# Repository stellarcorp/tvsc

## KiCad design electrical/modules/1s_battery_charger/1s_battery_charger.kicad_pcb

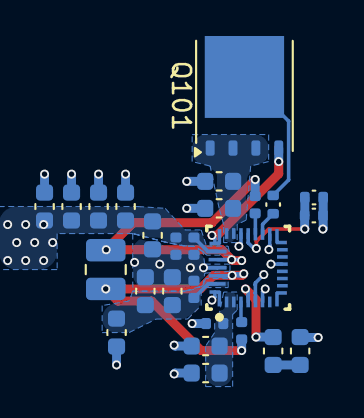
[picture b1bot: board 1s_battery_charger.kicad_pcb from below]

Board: 4 copper layers, 26 parts (26 on the bottom side), 15 nets.

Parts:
C101, C102, C104, C105, C107, C108, C111, C112, C114, C116, C117, C118, C119, C120: 10u; Nondescript_C_0603_1608Metric
C103, C106, C113, C115: 100n; Nondescript_C_0402_1005Metric
C109, C110: 0.047u; Nondescript_C_0402_1005Metric
L101: 2.2µH; L_1008_2520Metric
Q101: CSD16570Q5B; TDSON-8-1
R101, R102: 9k31; Nondescript_R_0402_1005Metric
R103: 100; Nondescript_R_0402_1005Metric
U101: BQ25798; RQM0029A-MFG

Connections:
/BATT_VIN: C101.1, C102.1, C103.1, U101.2 (VBUS), U101.3 (VBUS)
/REGN: C104.1, U101.5 (REGN), U101.17 (ILIM_HIZ)
/SYS: C113.1, C115.1, C116.1, C117.1, C118.1, C119.1, C120.1, U101.25 (SYS)
/VBATT: Q101.5 (D), R103.2
GND: C101.2, C102.2, C103.2, C105.2, C106.2, C107.2, C108.2, C111.2, C112.2, C113.2, C114.2, C115.2, C116.2, C117.2, C118.2, C119.2, C120.2, R101.2, R102.2, U101.13 (~CE), U101.27 (GND)
unnamed: C104.2, C105.1
unnamed: C111.1, C114.1, Q101.1 (S), Q101.2 (S), Q101.3 (S), U101.22 (BAT), U101.23 (BAT)
unnamed: Q101.4 (G), U101.24 (SDRV)
unnamed: R103.1, U101.18 (BATP)
unnamed: C109.1, U101.4 (BTST1)
unnamed: C110.1, U101.19 (BTST2)
unnamed: C106.1, C107.1, C108.1, C112.1, U101.29 (PMID)
unnamed: R101.1, R102.1, U101.20 (PROG)
unnamed: C109.2, L101.2, U101.28 (SW1)
unnamed: C110.2, L101.1, U101.26 (SW2)

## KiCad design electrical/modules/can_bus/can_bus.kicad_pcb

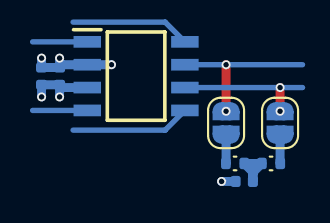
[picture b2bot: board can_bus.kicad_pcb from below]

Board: 4 copper layers, 8 parts (8 on the bottom side), 7 nets.

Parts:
C701: 1u; Nondescript_C_0402_1005Metric
C702, C703: 100n; Nondescript_C_0402_1005Metric
JP701, JP702: SolderJumper_2_Open; SolderJumper-2_P1.3mm_Open_RoundedPad1.0x1.5mm
R701, R702: 60; Nondescript_R_0402_1005Metric
U701: TCAN330DR; SOIC127P600X175-8N

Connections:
/3V3: C701.1, C702.1, U701.3 (VCC)
/CANH: JP701.1 (A), U701.7 (CANH)
/CANH_TERMINATION: JP701.2 (B), R701.1
/CANL: JP702.2 (B), U701.6 (CANL)
/CANL_TERMINATION: JP702.1 (A), R702.2
GND: C701.2, C702.2, C703.1, U701.2 (GND)
unnamed: C703.2, R701.2, R702.1

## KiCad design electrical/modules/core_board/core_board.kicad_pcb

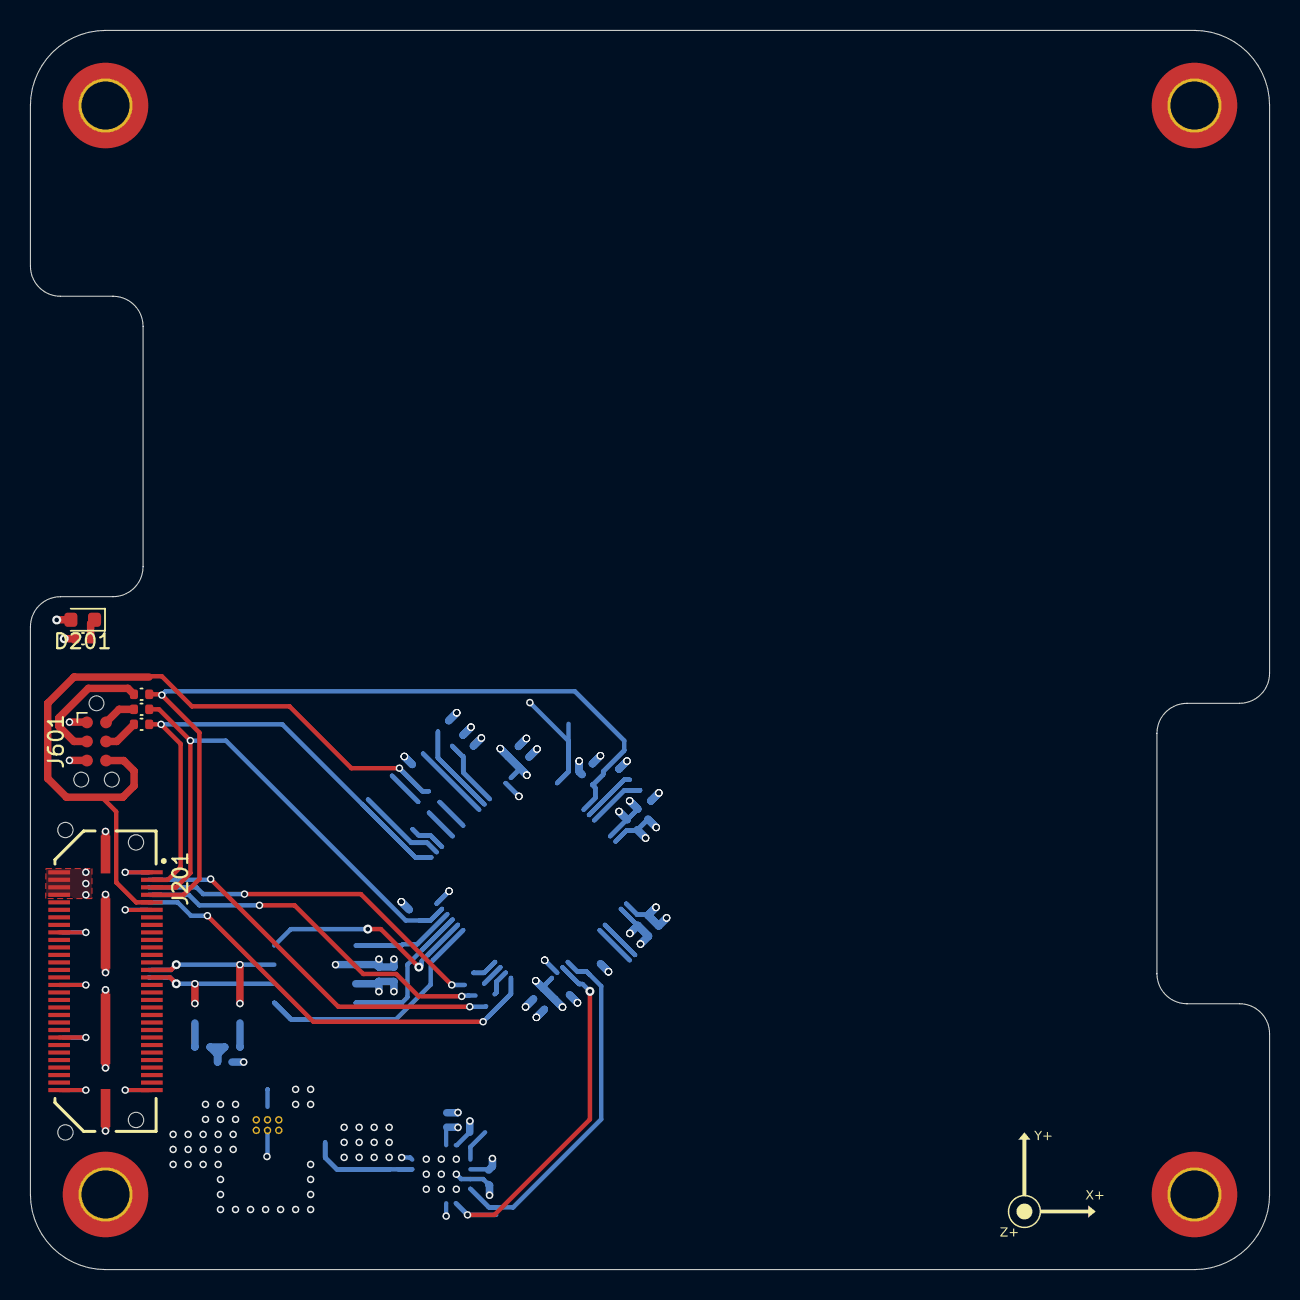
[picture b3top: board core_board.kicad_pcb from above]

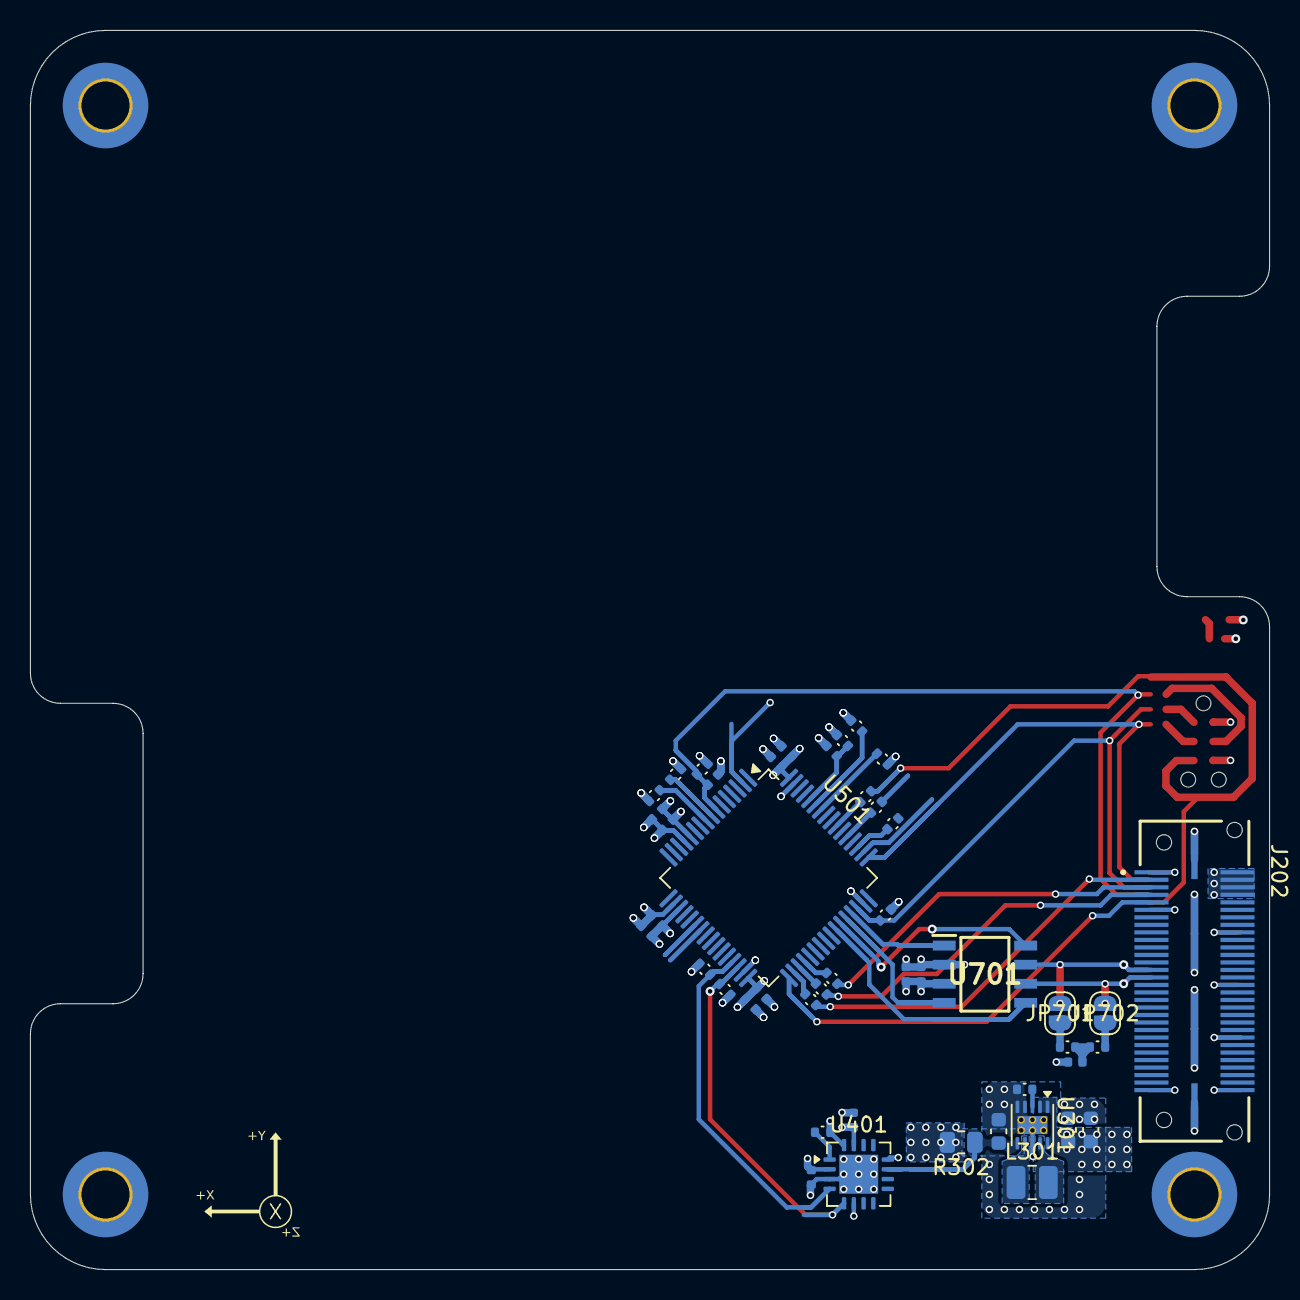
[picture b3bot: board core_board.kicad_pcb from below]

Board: 4 copper layers, 82.5 x 82.5 mm, 54 parts (46 on the bottom side), 44 nets.

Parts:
C301, C303: 22u; Nondescript_C_0603_1608Metric
C302: 10u; Nondescript_C_0603_1608Metric
C401, C402, C501, C502, C504, C506, C507, C509, C702, C703: 100n; Nondescript_C_0402_1005Metric
C503, C505, C508, C510, C701: 1u; Nondescript_C_0402_1005Metric
D201: Debug; LED_0603_1608Metric
J201: QTH-030-07-L-D-A; SAMTEC_QTH-030-07-L-D-A
J202: QSH-030-01-L-D-A; SAMTEC_QSH-030-01-L-D-A
J601: STLINK; Tag-Connect_TC2030-IDC-NL_2x03_P1.27mm_Vertical
JP701, JP702: SolderJumper_2_Open; SolderJumper-2_P1.3mm_Open_RoundedPad1.0x1.5mm
L301: 2.2µH; L_1008_2520Metric
PCB201: Core_Board
R201, R502, R503, R507, R508, R509, R514, R601, R602, R603: 33; Nondescript_R_0402_1005Metric
R301: 36k5; Nondescript_R_0402_1005Metric
R302: 100m; R_0805_2012Metric
R401, R501, R504, R505, R506, R510, R511, R512, R513, R515: 9k31; Nondescript_R_0402_1005Metric
R701, R702: 60; Nondescript_R_0402_1005Metric
U301: TPS63900; WSON-10-1EP_2.5x2.5mm_P0.5mm_EP1.2x2mm_ThermalVias
U401: PAC1934T-I/JQ; UQFN-16-1EP_4x4mm_P0.65mm_EP2.6x2.6mm
U501: STM32L452RCTx; LQFP-64_10x10mm_P0.5mm
U701: TCAN330DR; SOIC127P600X175-8N

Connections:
/3V3: C401.1, C402.1, C503.1, C504.1, C505.1, C506.1, C507.1, C508.1, C509.1, C510.1, C701.1, C702.1, J601.1 (T_VCC), R302.2, R401.1, R501.1, R504.1, R506.1, R510.1, R511.1, R512.1, R513.1, R515.1, U401.2 (V_{DD}), U401.12 (SENSE1-), U401.15 (V_{DD}IO), U401.16 (~PWRDN), U501.13 (VDDA), U501.19 (VDD), U501.32 (VDD), U501.64 (VDD), U701.3 (VCC)
/CAN bus/CANH_TERMINATION: JP701.2 (B), R701.1
/CAN bus/CANL_TERMINATION: JP702.1 (A), R702.2
/CAN bus/CAN_RX: U501.44 (PA11), U701.4 (RXD)
/CAN bus/CAN_SHUTDOWN: U501.42 (PA9), U701.5 (SHDN)
/CAN bus/CAN_SILENT: U501.43 (PA10), U701.8 (S)
/CAN bus/CAN_TX: U501.45 (PA12), U701.1 (TXD)
/CANH: J201.27, J202.27, JP701.1 (A), U701.7 (CANH)
/CANL: J201.29, J202.29, JP702.2 (B), U701.6 (CANL)
/CTRL.NRST: J202.07, R508.2
/CTRL.SWCLK: J202.03, R507.2
/CTRL.SWDIO: J202.05, R509.2
/CTRL.SWO: J202.09, U501.33 (PB12)
/I2C1_SCL: R511.2, U501.58 (PB6)
/I2C1_SDA: R515.2, U501.59 (PB7)
/I2C2_SCL: R510.2, U401.4 (SCL), U501.29 (PB10)
/I2C2_SDA: R512.2, U401.5 (SDA), U501.30 (PB11)
/I2C3_SCL: R501.2, U501.8 (PC0)
/I2C3_SDA: R506.2, U501.9 (PC1)
/MCU/BOOT0: C501.1, R505.1, U501.60 (PH3)
/MCU/DEBUG_LED: D201.2 (A), U501.2 (PC13)
/NRST: C502.1, J201.07, R504.2, R602.1, U501.7 (NRST)
/Power Measurement/BOARD_LOAD_+: C303.1, R302.1, U301.6 (VOUT), U401.11 (SENSE1+)
/SWCLK: J201.03, R603.1, U501.49 (PA14)
/SWDIO: J201.05, R513.2, R601.1, U501.46 (PA13)
/SWO: J201.09, J601.6 (T_SWO), R514.2
/VBUS: C301.1, C302.1, J201.01, J201.18, J201.32, J201.46, J201.60, J202.01, J202.18, J202.32, J202.46, J202.60, U301.1 (EN), U301.2 (SEL), U301.10 (VIN)
/VSOLAR: J201.02, J201.04, J201.06, J201.08, J202.02, J202.04, J202.06, J202.08
GND: C301.2, C302.2, C303.2, C401.2, C402.2, C501.2, C502.2, C503.2, C504.2, C505.2, C506.2, C507.2, C508.2, C509.2, C510.2, C701.2, C702.2, C703.1, J201.11, J201.59, J201.G1 (GND), J201.G2 (GND__1), J201.G3 (GND__2), J201.G4 (GND__3), J202.11, J202.59, J202.S1 (GND), J202.S2 (GND__1), J202.S3 (GND__2), J202.S4 (GND__3), J601.5 (GND), PCB201.MH1, PCB201.MH2, PCB201.MH3, PCB201.MH4, R201.2, R301.2, R505.2, U301.4 (CFG2), U301.5 (CFG3), U301.8 (GND), U301.11 (GND), U401.3 (GND), U401.6 (ADDRSEL), U401.17 (EP), U501.12 (VSSA), U501.18 (VSS), U501.31 (VSS), U501.47 (VSS), U501.63 (VSS), U701.2 (GND)
unnamed: C703.2, R701.2, R702.1
unnamed: D201.1 (K), R201.1
unnamed: J601.3 (T_NRST), R602.2
unnamed: J601.4 (T_SWCLK), R603.2
unnamed: J601.2 (T_SWDIO), R601.2
unnamed: R301.1, U301.3 (CFG1)
unnamed: L301.2, U301.9 (LX1)
unnamed: L301.1, U301.7 (LX2)
unnamed: R401.2, U401.1 (SLOW)
unnamed: R514.1, U501.55 (PB3)
unnamed: R507.1, U501.34 (PB13)
unnamed: R508.1, U501.35 (PB14)
unnamed: R509.1, U501.36 (PB15)
unnamed: R502.2, U501.51 (PC10)
unnamed: R503.2, U501.53 (PC12)

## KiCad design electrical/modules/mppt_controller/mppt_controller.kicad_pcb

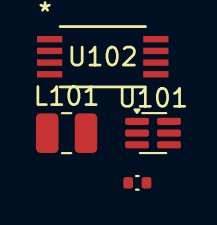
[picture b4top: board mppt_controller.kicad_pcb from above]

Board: 2 copper layers, 4 parts (0 on the bottom side), 5 nets, no tracks yet.

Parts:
L101: 2.2µH; L_1008_2520Metric
R101: 9k31; Nondescript_R_0402_1005Metric
U101: LM66100DCK; SOT-363_SC-70-6
U102: SPV1040TTR; SOIC_1040T_STM

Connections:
/VSOLAR: L101.2, U102.8 (XSHUT)
GND: R101.2, U101.2 (GND), U101.3 (~CE), U101.5 (ST), U102.2 (GND), U102.6 (ICTRL_MINUS), U102.7 (ICTRL_PLUS)
unnamed: U101.1 (VIN), U102.4 (VOUT)
unnamed: L101.1, U102.3 (LX)
unnamed: R101.1, U102.1 (MPP-SET)

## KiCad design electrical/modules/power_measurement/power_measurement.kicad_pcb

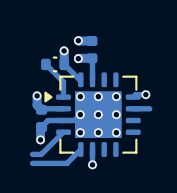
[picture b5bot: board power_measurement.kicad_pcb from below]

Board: 4 copper layers, 4 parts (4 on the bottom side), 3 nets.

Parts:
C401, C402: 100n; Nondescript_C_0402_1005Metric
R401: 9k31; Nondescript_R_0402_1005Metric
U401: PAC1934T-I/JQ; UQFN-16-1EP_4x4mm_P0.65mm_EP2.6x2.6mm

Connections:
/3V3: C401.1, C402.1, R401.1, U401.2 (V_{DD}), U401.12 (SENSE1-), U401.15 (V_{DD}IO), U401.16 (~PWRDN)
GND: C401.2, C402.2, U401.3 (GND), U401.6 (ADDRSEL), U401.17 (EP)
unnamed: R401.2, U401.1 (SLOW)
